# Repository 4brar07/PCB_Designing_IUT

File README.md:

# PCB_Designing_IUT
The PCBs I designed while being a student at IUT
I only recently started PCB designing, so I'm still learning. I'll keep track of my progress and share some of my projects here.
I mostly use Eagle for PCB, but I'm also learning to use Altium and plan on making it the primary software for designing.

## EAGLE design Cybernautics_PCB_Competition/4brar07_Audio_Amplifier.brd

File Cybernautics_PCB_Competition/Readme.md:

Cybernetics (a robotics and automation company in Bangladesh) sponsored the PCB Designing Contest in IUT.
This served as a great oppurtunity for students like me to get acquainted with PCB, and this is where
it all started for me. Cybernetics made history by developing the first-ever Made in Bangladesh military robot, now deployed in UN Peacekeeping Missions in the Democratic Republic of Congo and the Republic of Mali.

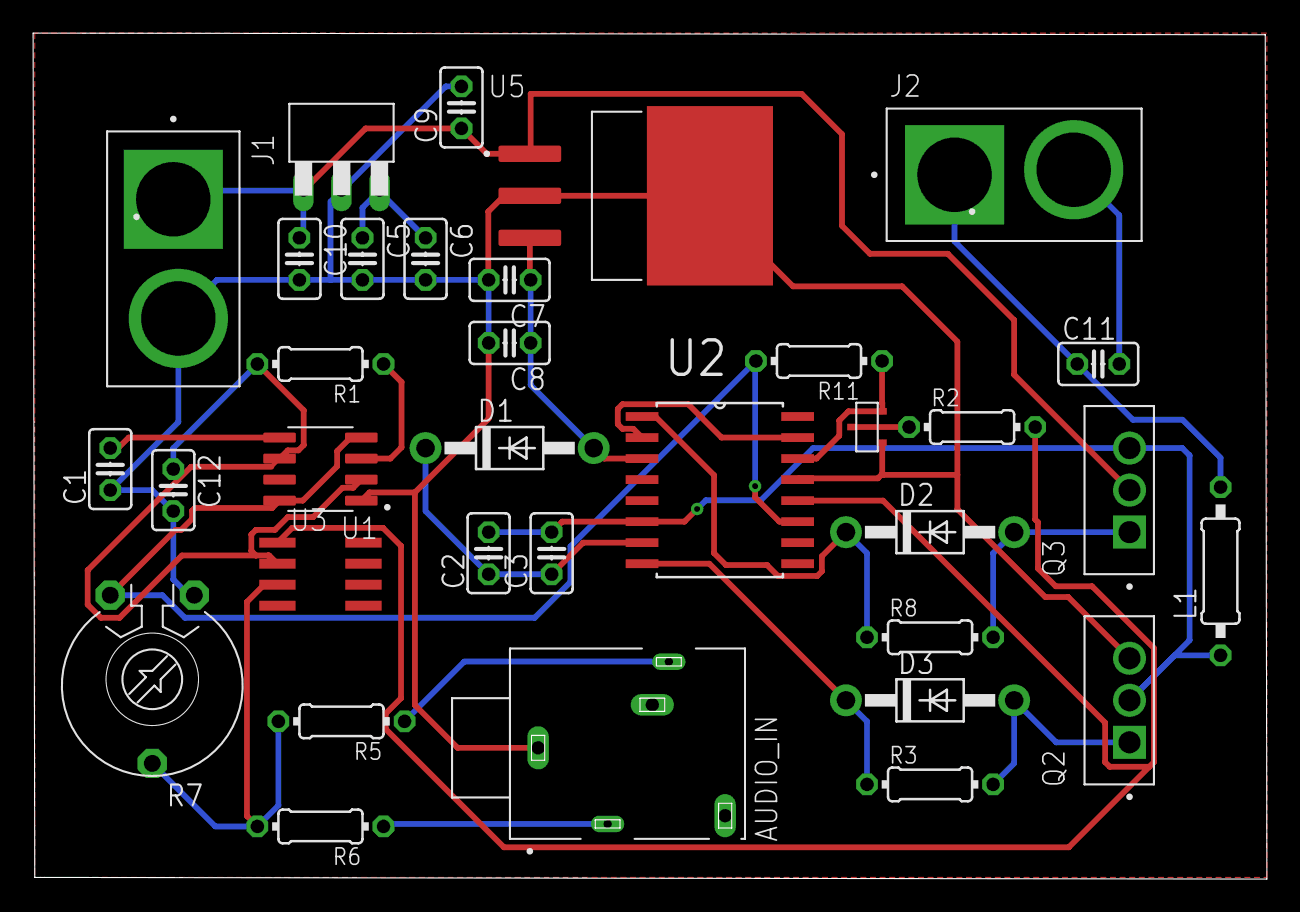
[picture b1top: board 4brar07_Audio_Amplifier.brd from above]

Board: 2 copper layers, 74.5 x 51.1 mm, 34 parts (0 on the bottom side), 23 nets.

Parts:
AUDIO_IN: PJ324M; WENZHOU_PJ324M
C1, C2, C3, C5, C6, C7, C8, C9, C10, C11, C12: C025-025X050
D1, D2, D3: 1N4004; DO41-10
J1, J2: XT60_YELLOW; AMASS_XT60PB-M
L1: 0207/10
Q2, Q3: IRF640NPBF; TO254P1067X483X2057-3
R1, R2, R3, R5, R6, R8, R11: 0204/7
R7: PT-10
T1: KTC8050S
TP7805Y3: TP7805Y3
U1: NE555DR; SOIC127P599X175-8N
U2: IR2110STRPBF; SOIC127P1032X265-16N
U3: LM358D; SO08
U5: LM7812S/NOPB; TO254P1524X483-4N

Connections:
6: C12.1, R1.2, U1.2, U1.6, U3.2
+5V: R7.2, R11.2, U1.4, U1.8, U2.11
+12V: C7.1, C8.1, D1.A, U2.3, U5.3
GND: AUDIO_IN.1, C1.1, C5.2, C6.2, C7.2, C8.2, C9.2, C10.2, C12.2, J1.2, Q2.3, R7.1, T1.E, TP7805Y3.2, U1.1, U2.13, U5.2, U5.4
HIN: R2.2, U2.12, U3.1
HO: D3.C, R3.1, U2.8
LIN: R11.1, T1.C, U2.14
LO: D2.C, R8.1, U2.1
unnamed: C11.1, J2.1, L1.2
unnamed: C11.2, J2.2
unnamed: C5.1, C6.1, TP7805Y3.3
unnamed: AUDIO_IN.2, R5.1
unnamed: D2.A, Q3.1, R8.2
unnamed: D3.A, Q2.1, R3.2
unnamed: R1.1, U1.3
unnamed: R5.2, R6.2, R7.3, U3.3
unnamed: AUDIO_IN.5, R6.1
unnamed: C1.2, U1.5
unnamed: R2.1, T1.B
VB: C2.1, C3.1, D1.C, U2.7
VIN: C9.1, C10.1, J1.1, Q3.2, TP7805Y3.1, U5.1
VS: C2.2, C3.2, L1.1, Q2.2, Q3.3, U2.6
VSS: U2.2, U2.15

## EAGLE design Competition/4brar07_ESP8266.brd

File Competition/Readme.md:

Cybernautics (a robotics and automation company in Bangladesh) sponsored the PCB Designing Contest in IUT.
This served as a great oppurtunity for students like me to get acquainted with PCB, and this is where
it all started for me. Cybernautics made history by developing the first-ever Made in Bangladesh military robot, now deployed in UN Peacekeeping Missions in the Democratic Republic of Congo and the Republic of Mali.

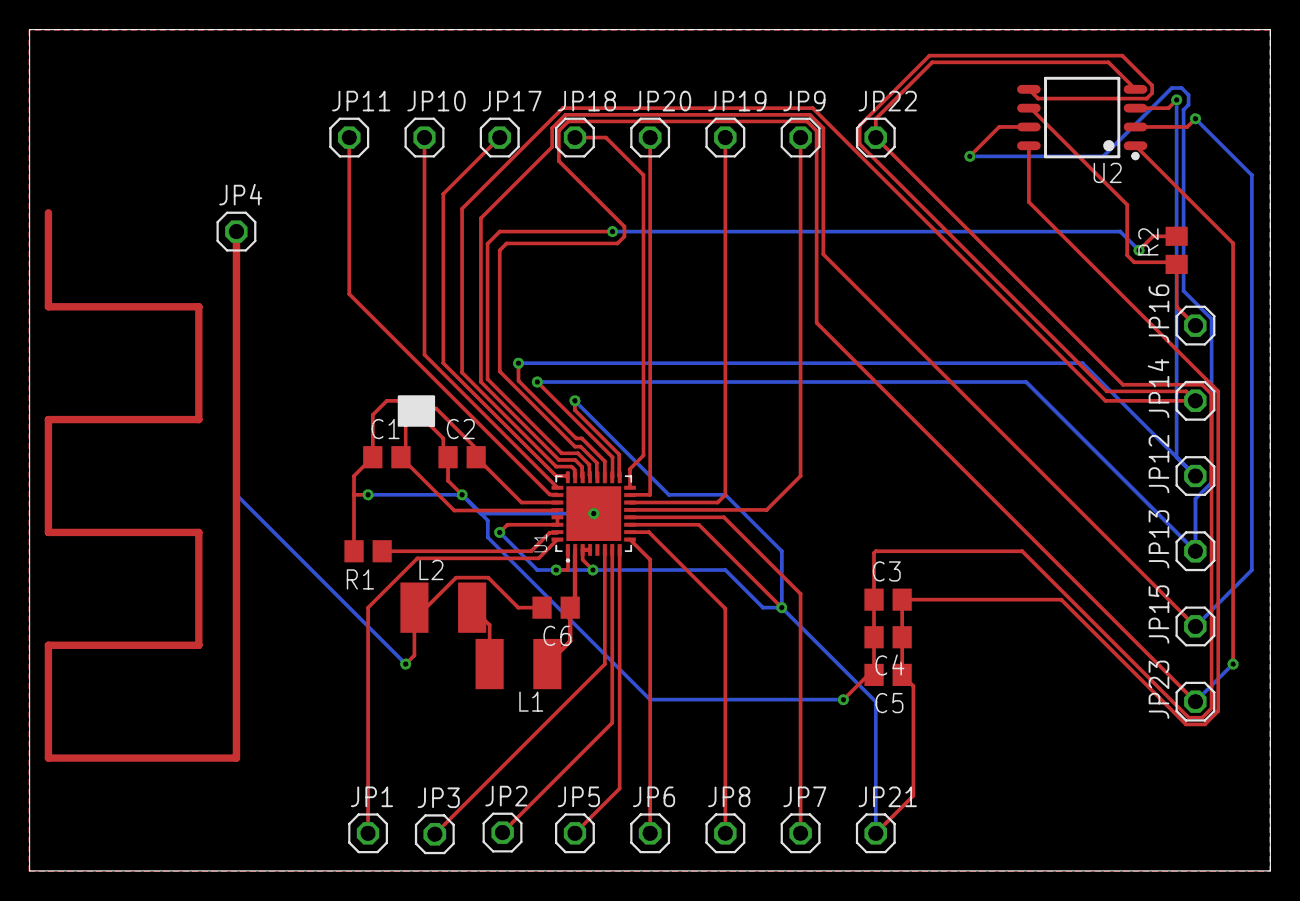
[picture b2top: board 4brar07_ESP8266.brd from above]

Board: 2 copper layers, 83.8 x 56.8 mm, 36 parts (0 on the bottom side), 29 nets.

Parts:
C1, C2, C3, C4, C5, C6: C0805
JP1, JP2, JP3, JP4, JP5, JP6, JP7, JP8, JP9, JP10, JP11, JP12, JP13, JP14, JP15, JP16, JP17, JP18, JP19, JP20, JP21, JP22, JP23: 1X01
L1, L2: L1812
R1, R2: R0805
U1: ESP8266EX; QFN50P500X500X80-33N
U2: W25Q32JVSSIQ; SOIC127P790X216-8N
U3: Q22FA12800332; OSCILLATOR

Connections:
ADC_IN: JP3.1, U1.6
ANT1: C6.2, JP4.1, L2.1
CHIP_ENABLE: JP2.1, U1.7
GND: C1.1, C2.1, C3.1, C4.2, C5.2, JP22.1, R1.2, U1.33, U2.4, U3.P$2, U3.P$4
GPIO0: JP20.1, U1.15
GPIO2: JP19.1, U1.14
GPIO4: JP18.1, U1.16
GPIO5: JP17.1, U1.24
GPIO12: JP8.1, U1.10
GPIO13: JP7.1, U1.12
GPIO14: JP6.1, U1.9
GPIO15: JP9.1, U1.13
GPIO16: JP5.1, U1.8
unnamed: C1.2, U1.28, U3.P$1
unnamed: C2.2, U1.27, U3.P$3
unnamed: C6.1, L1.1, U1.2
unnamed: R1.1, U1.31
unnamed: R2.2, U1.21
unnamed: L1.2, L2.2
RST: JP1.1, U1.32
SD_CLK: JP16.1, R2.1, U2.6
SD_CMD: JP23.1, U1.20, U2.1
SD_D0: JP15.1, U1.22, U2.2
SD_D1: JP14.1, U1.23, U2.5
SD_D2: JP13.1, U1.18, U2.7
SD_D3: JP12.1, U1.19, U2.3
URXD: JP10.1, U1.25
UTXD: JP11.1, U1.26
VDD33: C3.2, C4.1, C5.1, JP21.1, U1.1, U1.3, U1.4, U1.11, U1.17, U1.29, U1.30, U2.8

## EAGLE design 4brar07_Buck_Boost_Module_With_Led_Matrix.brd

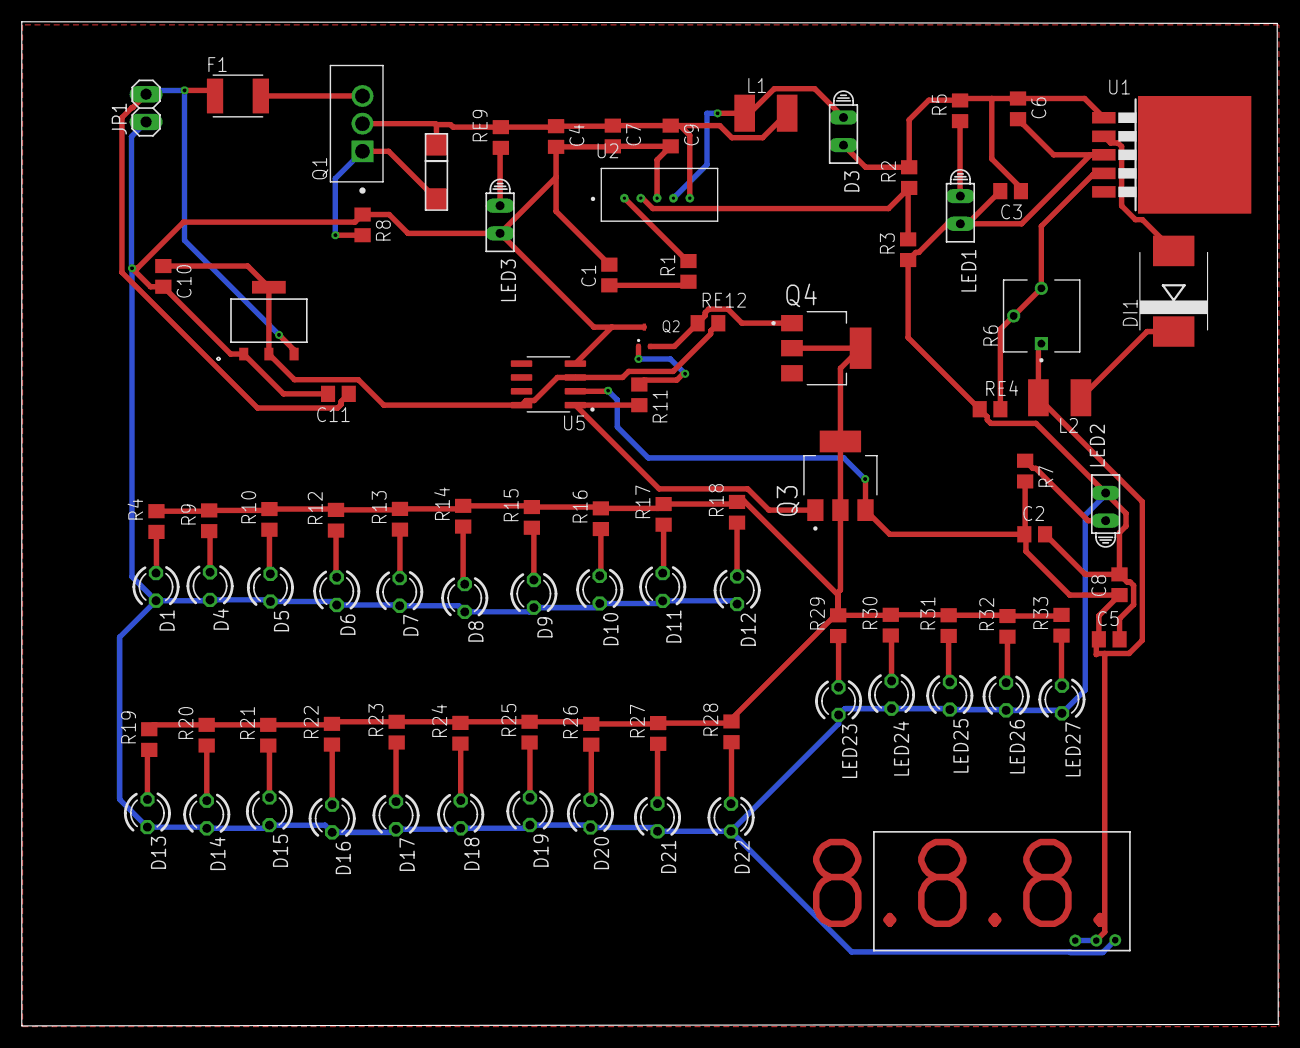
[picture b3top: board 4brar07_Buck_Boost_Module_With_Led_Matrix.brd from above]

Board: 2 copper layers, 115.3 x 92.2 mm, 91 parts (0 on the bottom side), 47 nets.

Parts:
C1, C2, C3, C4, C5, C6, C7, C8, C9, C10, C11: C0805
D1, D4, D5, D6, D7, D8, D9, D10, D11, D12, D13, D14, D15, D16, D17, D18, D19, D20, D21, D22: TLLG4400; LED3MM
D3: HLMP6
DI1: SS56SMC; SMC
DISP1: VOLTMETER
F1: MF-MSMF010-2; FUSER_MF-MSMF010-2
JP1: 1X02
L1, L2: L1812
LED1, LED2, LED3: HLMP6
LED23, LED24, LED25, LED26, LED27: TLLG4400; LED3MM
Q1: FQP47P06; TO254P1067X483X2286-3
Q2: BC847BV_115; SOT666
Q3, Q4: NTF5P03T3G; SOT230P700X175-4N
R1, R2, R3, R4, R5, R7, R8, R9, R10, R11, R12, R13, R14, R15, R16, R17, R18, R19, R20, R21, R22, R23, R24, R25, R26, R27, R28, R29, R30, R31, R32, R33: R0805
R6: 3362P-1-253LF; TRIM_3362P-1-253LF
RE4, RE9, RE12: R0805
U1: LM2596S; TO263-5
U2: LM2577T-ADJ; VREG_LM2577T-ADJ/NOPB
U4: AMS1117-5.0SOT223_AMS1117-5.0_ADS-L; SOT223_AMS1117-5.0_ADS-L
U5: LM358DR; SOIC127P599X175-8N
U$1: ZMM12

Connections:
4: D3.A, L1.1, U2.P$4
+5V: C10.1, RE12.2, U4.2, U4.4, U5.3, U5.8
FINAL: Q3.2, Q3.4, Q4.2, Q4.4, R4.2, R9.2, R10.2, R12.2, R13.2, R14.2, R15.2, R16.2, R17.2, R18.2, R19.2, R20.2, R21.2, R22.2, R23.2, R24.2, R25.2, R26.2, R27.2, R28.2, R29.2, R30.2, R31.2, R32.2, R33.2
GND: C1.2, C2.2, C3.2, C4.2, C5.2, C6.2, C7.2, C8.2, C9.2, C10.2, C11.2, D1.K, D4.K, D5.K, D6.K, D7.K, D8.K, D9.K, D10.K, D11.K, D12.K, D13.K, D14.K, D15.K, D16.K, D17.K, D18.K, D19.K, D20.K, D21.K, D22.K, DISP1.GND, JP1.1, LED1.K, LED2.K, LED3.K, LED23.K, LED24.K, LED25.K, LED26.K, LED27.K, Q2.5, R3.1, R8.1, RE4.1, U1.3, U2.P$3, U4.1, U5.4
unnamed: D1.A, R4.1
unnamed: F1.2, Q1.3
unnamed: C4.1, C7.1, C9.1, L1.2, Q1.2, RE9.2, U2.P$5, U$1.2
unnamed: Q1.1, R8.2, U$1.1
unnamed: D4.A, R9.1
unnamed: LED3.A, RE9.1
unnamed: C3.1, C6.1, D3.K, R2.2, R5.2, U1.1
unnamed: C1.1, R1.1
unnamed: R1.2, U2.P$1
unnamed: D5.A, R10.1
unnamed: D22.A, R28.1
unnamed: LED1.A, R5.1
unnamed: D21.A, R27.1
unnamed: Q2.1, R11.1
unnamed: D20.A, R26.1
unnamed: Q2.3, Q4.1, RE12.1
unnamed: DI1.A, U1.2
unnamed: DI1.C, L2.1
unnamed: D19.A, R25.1
unnamed: R6.2, R6.3, RE4.2, U1.4
unnamed: LED2.A, R7.1
unnamed: D18.A, R24.1
unnamed: Q3.1, R11.2, U5.1
unnamed: D6.A, R12.1
unnamed: LED23.A, R29.1
unnamed: LED24.A, R30.1
unnamed: LED25.A, R31.1
unnamed: LED26.A, R32.1
unnamed: LED27.A, R33.1
unnamed: D17.A, R23.1
unnamed: D16.A, R22.1
unnamed: D15.A, R21.1
unnamed: D14.A, R20.1
unnamed: D13.A, R19.1
unnamed: D7.A, R13.1
unnamed: D12.A, R18.1
unnamed: D11.A, R17.1
unnamed: D10.A, R16.1
unnamed: D9.A, R15.1
unnamed: D8.A, R14.1
unnamed: R2.1, R3.2, U2.P$2
OUT: C2.1, C5.1, C8.1, DISP1.MP, DISP1.VCC, L2.2, Q3.3, R6.1, R7.2, U5.2
VCC: C11.1, F1.1, JP1.2, U4.3

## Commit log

2025-10-18 Readme.md

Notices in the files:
parts and their libraries:
COPYRIGHT: Copyright (C) 2025 Ultra Librarian. All rights reserved.
